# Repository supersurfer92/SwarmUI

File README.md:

# BadukBot: Swarming robots to play the game Go/Baduk

Based on Zooids: Building Blocks for Swarm User Interfaces

Zooids, an open-source open-hardware platform for developing tabletop swarm interfaces, consist of a collection of custom-designed wheeled micro robots (each 2.6 cm in diameter), a radio base-station, a highspeed DLP structured light projector for optical tracking, and a software framework for application development and control.

Initial sketch of the redesigned Zooid, the BadukBot:

Revision 3 of the new pcb:

Original board:

BadukBot is based on Zooid software and hardware modified to play the game Go/Baduk/Weiqi. https://en.wikipedia.org/wiki/Go_(game)

Zooids in action: https://www.youtube.com/watch?time_continue=125&v=ZVdAfDMP3m0

## Hardware

The original Zooids are small custom-made robots as shown above; their dimensions are 26 mm in diameter, 21 mm in height
and they weight about 12 g. Each robot is powered by a 100 mAh LiPo battery and uses motor driven wheels. They contain a flexible elctrode for capacitive touch sensing. It communicates with the main computer through a NRF24L01+ chip on a separate receiver. Currently the limit for bots per receiver is 10. More can be added at a cost to performance/communication speed.

BadukBots are 22.5 mm in diameter and ~50 mm in height. Each bot is powered by a 200 mAh lipo battery with motor driven wheels.

The original Zooid files have been converted from Altium schematics to KiCAD from scratch based on the original Zooid schematic pdf (original files break when converted.) The new PCBs and schematics are located in the BadukBot directory. The Proto...BOM consolidates the components for bots, Receivers, chargers, and tools required into one sheet. The new BOM is mostly the same with changes to include prices, links, and modifications to quantities to make 81 (for a 9x9 board) and 361 (for a 19x19 board) bots in the Master BOM spreadsheet.

The PCB is designed using KiCAD and FreeRouting. The 3D files are created in MODO. The BadukBot breaks the design into 3 single boards that encase the battery to both make it possible to reflow at home and reduce the foot print to 22.5 mm from the Zooid's 26 mm (go stones are 22.5 mm and allow for a full 19x19 board to fit in the projection area.) Dimensions for bots and the playspace are based on https://senseis.xmp.net/?EquipmentDimensions and will be scaled if needed accordingly.

We may try other DLP Lightcrafter EVMs to reduce cost ($140 vs $1400.)

### Tracking
The system uses a projector-based tracking system for robot position tracking as shown below. Using a high frame rate (3000Hz) projector (DLP LightCrafter Evaluation Module) from Texas Instruments Inc., a sequence of gray-coded patterns are projected onto a flat surface. Then, the photodiodes on the robot independently decodes into a location within the projected area. 
The instruction for setting up this projector-based tracking system is included in the repository. 
There are other DLPLCEVM projectors available at lower resolutions and refresh rates ranging from $140 to $1600.

The play area will be mapped to make a main play area, a go bowl area and a capture pieces area

## Software

The communication structure consists of four main layers from highest to lowest level: Application, Simulation, Server, and Hardware. 

At the application level, the desired positions of the robots are computed. These desired positions are transmitted to
the simulation layer through a network socket. The application programmer can choose between two control strategies:
Proportional-Integral-Derivative (PID) position control or Hybrid Reciprocal Velocity Obstacles (HRVO) combined
with PID (these options are explained in the next paragraphs). Based on the chosen control strategy, the simulation layer
computes the goal positions of the robots, either final positions for PID or intermediate points for HRVO, and sends them to
the server. Finally, the server layer dispatches commands to the individual zooids, while at the same time monitoring their status and position.

Each robot independently controls its motion through a PID controller based on the state machine shown below. Given a final goal, the robot initially turns itself in the right direction and, once aligned, accelerates to its user-defined preferred speed. When it reaches the speed, it maintains it with a PID control on the orientation to ensure its direction towards the final goal. When a new incremental goal is given, it will still move at same speed but the PID control on orientation will direct the robot towards the new intermediate goal. When the robot arrives within 5 cm of the final goal, it slows down to its minimum velocity and once within 1 cm of the final goal, it stops and orients itself as commanded by the application programmer. To enable smooth transitions between the incremental goal positions, robots are given their next position at 60 Hz.

The modified software for playing Go using SwarmUI (GoSwarm) can be found at https://github.com/nheyn/GoSwarm and https://github.com/nheyn/react-swarm-ui and modified firmware will be maintained in this repo.

Goals include:

-defined areas for the bots including game play area on a grid

-automatically arranging bots to a Go bowl area

-automatically moving captured stones/bots to a defined captured bowl area

-queueing bots for the next turn

-game play rules like passing/resigning

-automatic scoring (and the ability to adjust captured areas)

-the ability to show which player is the winner (2 bots emerge from the winners go bowl, 1 from the loser after both sides pass or one resigns)

Resources and goals for features can be found at https://github.com/supersurfer92/SwarmUI-BadukBots/blob/master/Software/Go%20Features%2C%20Programming%20Gits%2C%20and%20theory.txt

GoSwarm has rewritten the ZooidManager program from C++ to Java and is currently developing swarming functions

## Acknowledgments 

BadukBot and GoSwarm/react-SwarmUI is a hobby project created by Caleb Cover and Nick Heyn based on SwarmUI.

The original SwarmUI project (https://github.com/ShapeLab/SwarmUI) is a joint work between the Shape Lab at Stanford University (USA) and the Aviz team at Inria (France). It was partially funded by the Région Ile de France, DIM ISC-PIF. We would also like to thank Alexa Siu, Shenli Yuan, Ernesto Ramirez and Pham Minh Hieu for investing so much time and efforts in making this work possible. 

The original licenses are retained where applicable and the licenses used for new hardware developed will use a license that follows the Open Source Hardware Association definition of Open Source Hardware (https://www.oshwa.org/definition/.)

<br />This work is licensed under a <a rel="license" href="http://creativecommons.org/licenses/by-sa/4.0/">Creative Commons Attribution-ShareAlike 4.0 International License</a>.

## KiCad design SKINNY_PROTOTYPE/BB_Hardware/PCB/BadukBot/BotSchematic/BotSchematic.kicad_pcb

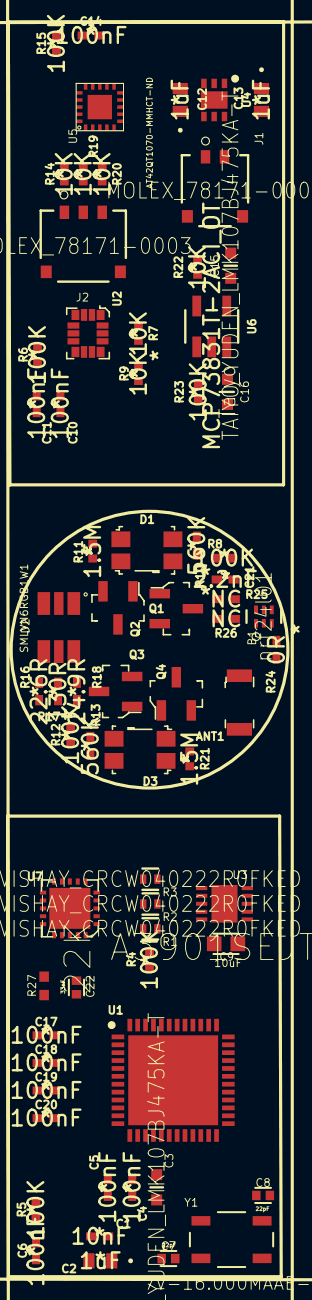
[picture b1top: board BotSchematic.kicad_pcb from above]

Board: 4 copper layers, 68 parts (0 on the bottom side), 52 nets, no tracks yet.

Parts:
ANT1: Antenna; Antenna_1.6x3.2mm_2450AT18A100E
B1: nrf24l01; JOHANSON_2450BM14A0002T_0
C1: 10nF; C0402C103J3RACTU
C2, C12, C13: 1uF; 0603ZD105KAT2A
C3, C15: TAIYO_YUDEN_LMK107BJ475KA-T; TAIYO_YUDEN_LMK107BJ475KA-T_0
C4, C5, C6, C10, C11, C14, C17, C18, C19, C20: 100nF; C0402C104K4RACTU
C7, C8: 22pF; CAPC1005X55N
C9: 10uF; CAPC1608X9N
C16: Taiyo; TAIYO_YUDEN_LMK107BJ475KA-T_0
C21: 2.2nF; C0402C222K5RACTU
C22: 33nF; CAPC1005X55N
D1, D3: PD15-22C_TR8; SMD-4_3.3x2.8_PD15-22C_TR8
D2: SMLVN6RGB1W1; LED310X280X60-6N
J1: MOLEX_78171-0002; MOLEX_78171-0002_0
J2: MOLEX_78171-0003; MOLEX_78171-0003_0
Q1, Q2, Q3, Q4: MMBT3904LT1G; SOT-23-3
R1, R2, R3: VISHAY_CRCW040222R0FKED; VISHAY_CRCW040222R0FKED_0
R4, R5, R6, R8, R12, R15, R23: 100K; CRCW0402100KFKED
R7, R9, R14, R19, R20, R22: 10K; CRCW040210K0FKED
R10, R13: 560K; RC0402FR-07560KL
R11, R21: 1.5M; CRCW04021M50FKED
R16: 22.6R; ERJ-2RKF22R6X
R17: 130R; ERJ-2RKF1300X
R18: 24.9R; ERJ-2RKF24R9X
R24: 0R; ERJ-2GE0R00X
R25, R26: NC; ERJ-2GE0R00X
R27: 22K; RESC1005X40N
U1: STM32F051C8U6; QFN50P700X700X65-49N-D
U2: LSM6DS3; LGA-14L_2.5x3mm__LSM6DS3
U3: A3901SEJTR-T; DFN300X300X75-11N
U4: ADP122ACPZ-3.3-R7; SON65P200X200X60-7N-D
U5: AT42QT1070-MMHCT-ND; VQFN_20PAD
U6: MCP73831T-2ACI_OT; MCP73831T-2ACI&slash_OT
U7: NRF24L01P-R7; QFN-20-1EP_4x4mm_RevA
Y1: 7V-16.000MAAE-T; OSCCC500X320X105N

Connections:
+3V3: C1.1, C2.1, C3.1, C4.1, C5.1, C9.1, C10.1, C11.1, C13.1, C14.1, C17.2, C18.2, C19.2, C20.2, D1.K, D2.1, D2.2, D2.3, D3.K, R5.2, R6.2, R7.2, R8.2, R9.2, R10.2, R12.2, R13.2, R15.2, R23.1, U1.9, U1.24, U1.48, U2.5, U2.8, U2.12, U3.8, U4.1, U5.9, U5.13, U7.7, U7.15, U7.18
+BATT: C12.1, C16.1, J1.1, U1.1, U4.4, U4.6, U6.3
ANT1: B1.4, U7.12
ANT2: B1.3, U7.13
CSN: U1.14, U7.2
Charging: R23.2, U6.1
GND: B1.2, C1.2, C2.2, C3.2, C4.2, C5.2, C6.2, C7.2, C8.2, C9.2, C10.2, C11.2, C12.2, C13.2, C14.2, C15.2, C16.2, C17.1, C18.1, C19.1, C20.1, C21.2, C22.2, J1.2, Q1.2, Q2.2, Q3.2, Q4.2, R4.2, R11.2, R21.1, R22.1, R25.2, R26.2, R27.1, U1.8, U1.23, U1.47, U1.49, U2.1, U2.2, U2.3, U2.6, U2.7, U3.3, U4.3, U5.8, U5.11, U6.2, U7.8, U7.14, U7.17, U7.20, U7.21
IMU_INT: R6.1, U1.25, U2.4
MCU_X1_16MHZ: C7.1, U1.5, Y1.1
MCU_X2_16MHZ: C8.1, U1.6, Y1.3
MISO: U1.16, U7.5
MOSI: U1.17, U7.4
MOTOR_CONTROL1: U1.10, U3.1
MOTOR_CONTROL2: U1.11, U3.2
MOTOR_CONTROL3: U1.12, U3.4
MOTOR_CONTROL4: U1.13, U3.5
NRST: C6.1, R2.2, R5.1
unnamed: ANT1.1, R24.1, R26.1
unnamed: B1.1, R24.2, R25.1
unnamed: C15.1, U6.4
unnamed: C22.1, U7.19
unnamed: D1.A, Q2.1, R11.1
unnamed: D2.4, R16.2
unnamed: D2.5, R17.2
unnamed: D2.6, R18.2
unnamed: D3.A, Q4.1, R21.2
unnamed: J2.1, R14.2
unnamed: J2.2, R19.2
unnamed: J2.3, R20.2
unnamed: Q1.1, Q2.3, R10.1
unnamed: Q3.1, Q4.3, R13.1
unnamed: R4.1, U1.44
unnamed: R14.1, U5.4
unnamed: R19.1, U5.3
unnamed: R20.1, U5.2
unnamed: R22.2, U6.5
unnamed: R27.2, U7.16
PHOTODIODE_1: Q1.3, R8.1, U1.46
PHOTODIODE_2: Q3.3, R12.1, U1.19
RADIO_CE: U1.18, U7.1
RADIO_CLK: U1.29, U7.10
RADIO_IRQ: U1.38, U7.6
RGBLED1: R17.1, U1.31
RGBLED2: R16.1, U1.32
RGBLED3: R18.1, U1.30
SCK: U1.15, U7.3
SCL: R9.1, U1.21, U1.42, U2.13, U5.15
SDA: R7.1, U1.22, U1.43, U2.14, U5.12
SWCLK: R3.2, U1.37
SWDIO: R1.2, U1.34
VDD_PA: B1.5, C21.1, U7.11
~TOUCH_CHG~: R15.1, U5.14

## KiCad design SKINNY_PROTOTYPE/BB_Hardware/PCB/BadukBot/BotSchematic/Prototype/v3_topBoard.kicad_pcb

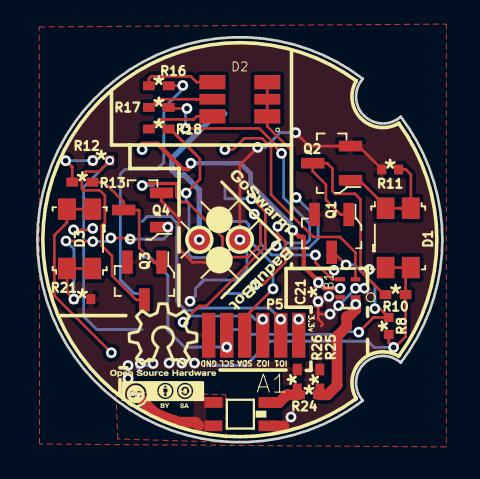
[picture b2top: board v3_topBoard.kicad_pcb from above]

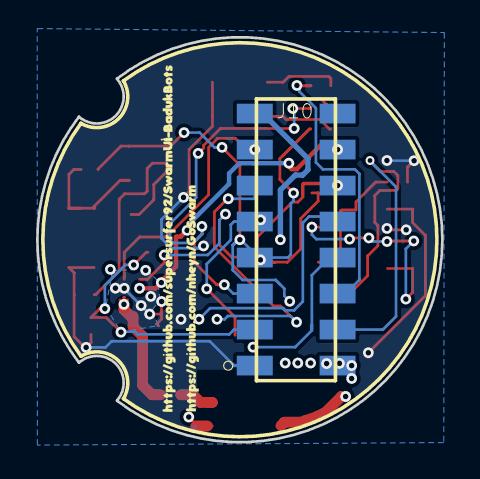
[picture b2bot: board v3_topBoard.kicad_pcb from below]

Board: 2 copper layers, 22.5 x 22.5 mm, 28 parts (2 on the bottom side), 24 nets.

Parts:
A1: 2450AT18D0100E; DFN320X160X120-4RN
B1: nrf24l01; JOHANSON_2450BM14A0002T_0
C21: 2.2nF; C0402C222K5RACTU
D1, D3: PD15-22C_TR8; SMD-4_3.3x2.8_PD15-22C_TR8
D2: SMLVN6RGB1W1; LED310X280X60-6N
G1: LOGO; BadukBot-GoSwarm
G2: LOGO; OpenHardwareLogo
G7: LOGO; links_20mm
J10: A316DA2SV71; A13_1
P4: Conn01x02Female; Conn_01x02_Female
P5: Pads; ExternalPort
Q1, Q2, Q3, Q4: MMBT3904LT1G; SOT-23-3
R8, R12: 100K; CRCW0402100KFKED
R10, R13: 560K; RC0402FR-07560KL
R11, R21: 1.5M; CRCW04021M50FKED
R16: 22.6R; ERJ-2RKF22R6X
R17: 130R; ERJ-2RKF1300X
R18: 24.9R; ERJ-2RKF24R9X
R24: 0R; ERJ-2GE0R00X
R25, R26: NC; ERJ-2GE0R00X

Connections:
1a33v: D1.K, D2.1, D2.2, D2.3, D3.K, J10.1, P5.1, R8.2, R10.2, R12.2, R13.2
2aGND: A1.2, A1.3, A1.4, B1.2, C21.2, J10.2, J10.16, P4.2, P5.6, Q1.2, Q2.2, Q3.2, Q4.2, R11.2, R21.1, R25.2, R26.2
3aPHOTODIODE1: J10.3, Q1.3, R8.1
4aPHOTODIODE2: J10.4, Q3.3, R12.1
5aRGBLED1: J10.5, R17.1
6aRGBLED2: J10.6, R16.1
7aRGBLED3: J10.7, R18.1
12aA1: B1.4, J10.12
13aA2: B1.3, J10.13
14aVDDPA: B1.5, C21.1, J10.14
15aP41: J10.15, P4.1
unnamed: A1.1, R24.1, R26.1
unnamed: B1.1, R24.2, R25.1
unnamed: D1.A, Q2.1, R11.1
unnamed: D2.4, R16.2
unnamed: D2.5, R17.2
unnamed: D2.6, R18.2
unnamed: D3.A, Q4.1, R21.2
unnamed: J10.8, P5.5
unnamed: J10.9, P5.4
unnamed: J10.10, P5.2
unnamed: J10.11, P5.3
unnamed: Q1.1, Q2.3, R10.1
unnamed: Q3.1, Q4.3, R13.1

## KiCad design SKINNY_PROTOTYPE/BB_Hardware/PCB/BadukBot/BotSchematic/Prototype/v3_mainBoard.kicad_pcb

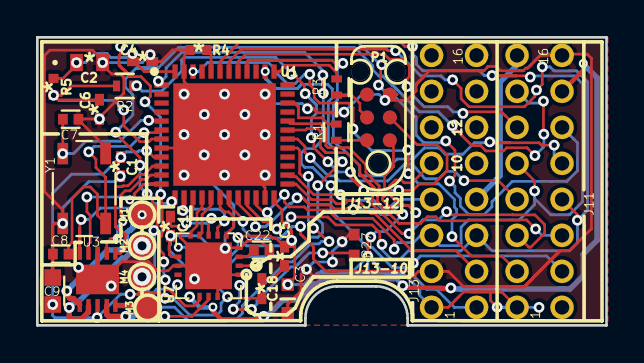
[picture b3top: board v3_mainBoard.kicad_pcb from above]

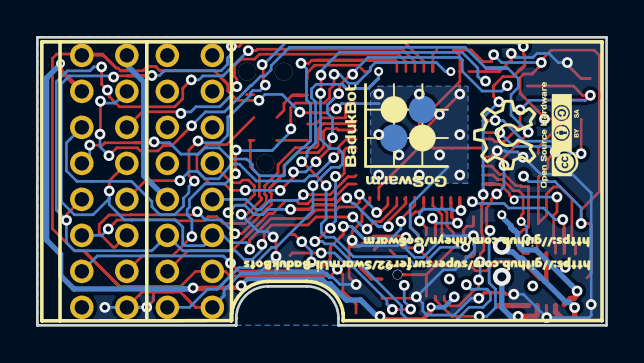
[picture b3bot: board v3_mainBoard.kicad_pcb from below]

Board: 2 copper layers, 31.6 x 16.0 mm, 33 parts (4 on the bottom side), 44 nets.

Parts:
C1: 10nF; C0402C103J3RACTU
C2: 1uF; 0603ZD105KAT2A
C3: TAIYO_YUDEN_LMK107BJ475KA-T; TAIYO_YUDEN_LMK107BJ475KA-T_0
C4, C5, C6, C17, C18: 100nF; C0402C104K4RACTU
C7, C8: 22pF; CAPC1005X55N
C9: 10uF; CAPC1608X9N
C22: 33nF; CAPC1005X55N
G1: LOGO; BadukBot-GoSwarm
G2: LOGO; OpenHardwareLogo
G5: LOGO; links_20mm
J11, J13: 62401621722; 0877601616
M1: Pos1a; TESTPOINT-50MIL
M2: Neg1a; TESTPOINT-50MIL
M3: Pos2a; TESTPOINT-50MIL
M4: Neg2a; TESTPOINT-50MIL
P1: SWDPads; SWD_6pin
P4: Conn_01x02_Female
R1, R2, R3: VISHAY_CRCW040222R0FKED; VISHAY_CRCW040222R0FKED_0
R4, R5: 100K; CRCW0402100KFKED
R27: 22K; RESC1005X40N
U1: STM32F051C8U6; QFN50P700X700X65-49N-D
U3: A3901SEJTRT; DFN300X300X75-11N
U7: NRF24L01PR7; QFN-20-1EP_4x4mm_RevA
Y1: 7V16000MAAET; OSCCC500X320X105N

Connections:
1b33v: C1.1, C2.1, C3.1, C4.1, C5.1, C9.1, C17.2, C18.2, J11.1, J13.1, P1.1, R5.2, U1.9, U1.24, U1.48, U3.8, U7.7, U7.15, U7.18
2bGND: C1.2, C2.2, C3.2, C4.2, C5.2, C6.2, C7.2, C8.2, C9.2, C17.1, C18.1, C22.2, J11.16, J13.3, P1.5, R4.2, R27.1, U1.8, U1.23, U1.47, U1.49, U3.3, U3.11, U7.8, U7.14, U7.17, U7.20, U7.21, Y1.2, Y1.4
3bPHOTODIODE1: J11.3, U1.46
4bPHOTODIODE2: J11.4, U1.19
5bRGBLED1: J11.5, U1.31
6bRGBLED2: J11.6, U1.32
7bRGBLED3: J11.7, U1.30
8bIO1: J11.10, U1.40
9bIO2: J11.11, U1.41
10bSDA: J11.9, J13.5, U1.22, U1.43
11bSCL: J11.8, J13.6, U1.21, U1.42
12bA1: J11.12, U7.12
13bA2: J11.13, U7.13
14bVDDPA: J11.14, U7.11
15bP41: J11.15, J13.8
22bVBAT: J13.2, U1.1
24bIMUINT: J13.4, U1.25
27bCHARGING: J13.7, U1.26
CSN: U1.14, U7.2
MCUX116MHZ: C7.1, U1.5, Y1.1
MCUX216MHZ: C8.1, U1.6, Y1.3
MISO: U1.16, U7.5
MOSI: U1.17, U7.4
MOTORCONTROL1: U1.10, U3.1
MOTORCONTROL2: U1.11, U3.2
MOTORCONTROL3: U1.12, U3.4
MOTORCONTROL4: U1.13, U3.5
NRST: C6.1, R2.2, R5.1, U1.7
unnamed: C22.1, U7.19
unnamed: M1.1, U3.6
unnamed: M2.1, U3.7
unnamed: M3.1, U3.10
unnamed: M4.1, U3.9
unnamed: P1.2, R1.1
unnamed: P1.3, R2.1
unnamed: P1.4, R3.1
unnamed: R4.1, U1.44
unnamed: R27.2, U7.16
RADIOIRQ: U1.38, U7.6
RADIO_CE: U1.18, U7.1
SCK: U1.15, U7.3
SWCLK: R3.2, U1.37
SWDIO: R1.2, U1.34
~29bTOUCHCHG~: J13.9, U1.20

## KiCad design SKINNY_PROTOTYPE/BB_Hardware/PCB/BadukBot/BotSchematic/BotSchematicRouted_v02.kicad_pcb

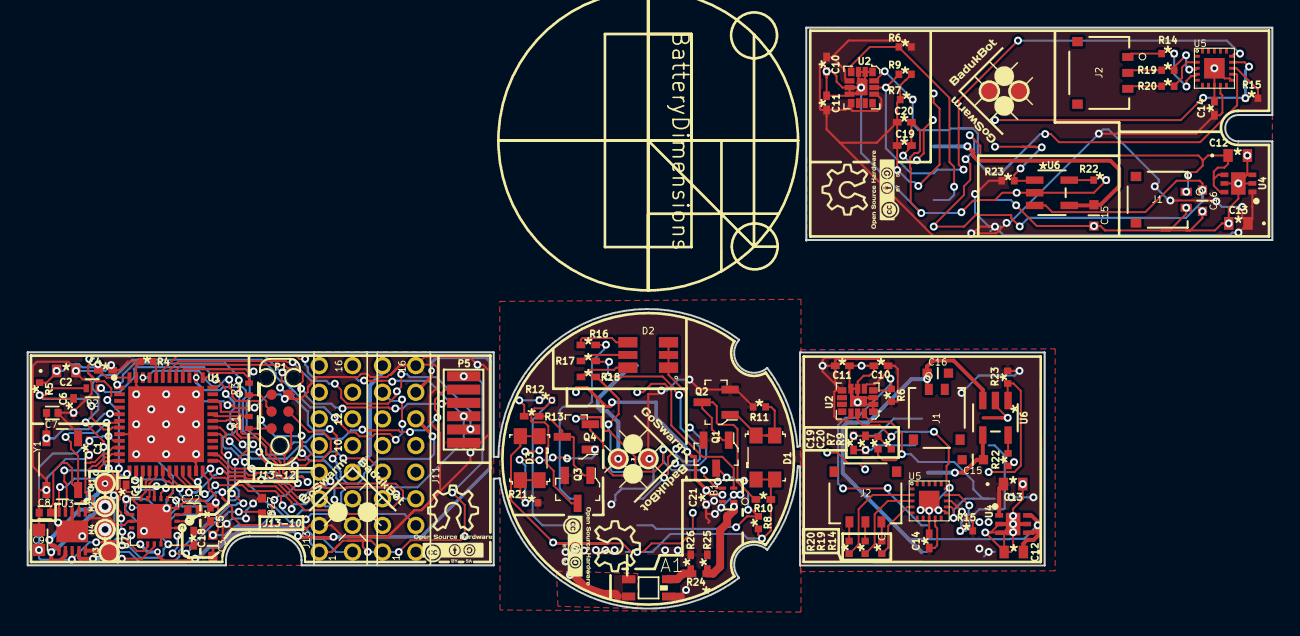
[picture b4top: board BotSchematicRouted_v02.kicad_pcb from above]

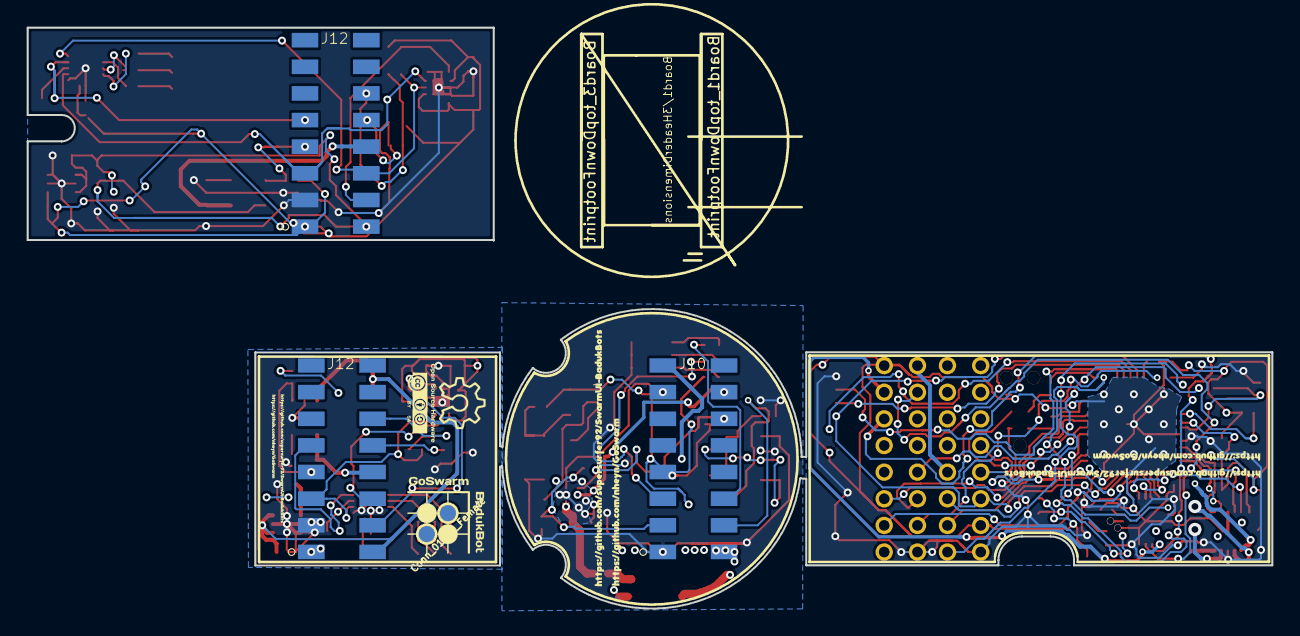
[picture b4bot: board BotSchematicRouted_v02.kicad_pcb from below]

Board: 2 copper layers, 93.5 x 43.6 mm, 117 parts (8 on the bottom side), 106 nets.

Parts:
A1: 2450AT18D0100E; DFN320X160X120-4RN
B1: nrf24l01; JOHANSON_2450BM14A0002T_0
C1: 10nF; C0402C103J3RACTU
C2, C12, C12#2, C13, C13#2: 1uF; 0603ZD105KAT2A
C3, C15, C15#2: TAIYO_YUDEN_LMK107BJ475KA-T; TAIYO_YUDEN_LMK107BJ475KA-T_0
C4, C5, C6, C10, C10#2, C11, C11#2, C14, C14#2, C17, C18: 100nF; C0402C104K4RACTU
C7, C8: 22pF; CAPC1005X55N
C9: 10uF; CAPC1608X9N
C16, C16#2: Taiyo; TAIYO_YUDEN_LMK107BJ475KA-T_0
C19, C19#2: 10nF; C0402C104K4RACTU
C20, C20#2: 1nF; C0402C104K4RACTU
C21: 2.2nF; C0402C222K5RACTU
C22: 33nF; CAPC1005X55N
D1, D3: PD15-22C_TR8; SMD-4_3.3x2.8_PD15-22C_TR8
D2: SMLVN6RGB1W1; LED310X280X60-6N
G1, G1#2, G1#3, G11: LOGO; BadukBot-GoSwarm
G2, G2#2, G2#3, G10: LOGO; OpenHardwareLogo
G5, G7: LOGO; links_20mm
J1, J1#2: MOLEX781710002; MOLEX_78171-0002_0
J2, J2#2: MOLEX781710003; MOLEX_78171-0003_0
J10, J12, J12#2: A316DA2SV71; A13_1
J11: 62401621722; 0877601616
J13: 0877601616
M1: Pos1a; TESTPOINT-50MIL
M2: Neg1a; TESTPOINT-50MIL
M3: Pos2a; TESTPOINT-50MIL
M4: Neg2a; TESTPOINT-50MIL
P1: SWDPads; SWD_6pin
P4: Conn01x02Female; Conn_01x02_Female
P5: Pads; ExternalPort
P10: Conn_01x02_Female
Q1, Q2, Q3, Q4: MMBT3904LT1G; SOT-23-3
R1, R2, R3: VISHAY_CRCW040222R0FKED; VISHAY_CRCW040222R0FKED_0
R4, R5, R6, R6#2, R8, R12, R15, R15#2, R23, R23#2: 100K; CRCW0402100KFKED
R7, R7#2, R9, R9#2, R14, R14#2, R19, R19#2, R20, R20#2, R22, R22#2: 10K; CRCW040210K0FKED
R10, R13: 560K; RC0402FR-07560KL
R11, R21: 1.5M; CRCW04021M50FKED
R16: 22.6R; ERJ-2RKF22R6X
R17: 130R; ERJ-2RKF1300X
R18: 24.9R; ERJ-2RKF24R9X
R24: 0R; ERJ-2GE0R00X
R25, R26: NC; ERJ-2GE0R00X
R27: 22K; RESC1005X40N
TESTPOINT-50MIL, TESTPOINT-50MIL#2: VAL**; TESTPOINT-50MIL
U1: STM32F051C8U6; QFN50P700X700X65-49N-D
U2, U2#2: LSM6DS3; LGA-14L_2.5x3mm__LSM6DS3
U3: A3901SEJTRT; DFN300X300X75-11N
U4, U4#2: ADP122ACPZ33R7; SON65P200X200X60-7N-D
U5, U5#2: AT42QT1070MMHCTND; VQFN_20PAD
U6, U6#2: MCP73831T2ACIOT; MCP73831T-2ACI&slash_OT
U7: NRF24L01PR7; QFN-20-1EP_4x4mm_RevA
Y1: 7V16000MAAET; OSCCC500X320X105N

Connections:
1a33v: D1.K, D2.1, D2.2, D2.3, D3.K, J10.1, R8.2, R10.2, R12.2, R13.2
1b33v: C1.1, C2.1, C3.1, C4.1, C5.1, C9.1, C17.2, C18.2, J11.1, J13.1, P1.1, P5.1, R5.2, U1.9, U1.24, U1.48, U3.8, U7.7, U7.15, U7.18
2aGND: A1.2, A1.3, A1.4, B1.2, C21.2, J10.2, P4.2, Q1.2, Q2.2, Q3.2, Q4.2, R11.2, R21.1, R25.2, R26.2
2bGND: C1.2, C2.2, C3.2, C4.2, C5.2, C6.2, C7.2, C8.2, C9.2, C17.1, C18.1, C22.2, J11.16, J13.3, P1.5, P5.6, R4.2, R27.1, U1.8, U1.23, U1.47, U1.49, U3.3, U3.11, U7.8, U7.14, U7.17, U7.20, U7.21, Y1.2, Y1.4
3aPHOTODIODE1: J10.3, Q1.3, R8.1
3bPHOTODIODE1: J11.3, U1.46
4aPHOTODIODE2: J10.4, Q3.3, R12.1
4bPHOTODIODE2: J11.4, U1.19
5aRGBLED1: J10.5, R17.1
5bRGBLED1: J11.5, U1.31
6aRGBLED2: J10.6, R16.1
6bRGBLED2: J11.6, U1.32
7aRGBLED3: J10.7, R18.1
7bRGBLED3: J11.7, U1.30
8bIO1: P5.2, U1.40
9bIO2: P5.3, U1.41
10bSDA: J13.5, P5.4, U1.22, U1.43
11bSCL: J13.6, P5.5, U1.21, U1.42
12aA1: B1.4, J10.12
12bA1: J11.12, U7.12
13aA2: B1.3, J10.13
13bA2: J11.13, U7.13
14aVDDPA: B1.5, C21.1, J10.14
14bVDDPA: J11.14, U7.11
15aP41: J10.15, P4.1
15bP41: J11.15, J13.8
21a3.3v: R7.2, R7#2.2, R9.2, R9#2.2
21a33v: C10.1, C10#2.1, C11.1, C11#2.1, C13.1, C13#2.1, C14.1, C14#2.1, C19.2, C19#2.2, C20.2, C20#2.2, J12.1, J12#2.1, R6.2, R6#2.2, R15.2, R15#2.2, R23.1, R23#2.1, U2.5, U2.8, U2.12, U2#2.5, U2#2.8, U2#2.12, U4.1, U4#2.1
22aVBAT: C12.1, C12#2.1, C16.1, C16#2.1, J1.1, J1#2.1, J12.2, J12#2.2, U4.4, U4.6, U4#2.4, U4#2.6, U6.3, U6#2.3
22bVBAT: J13.2, U1.1
23aGround: C10.2, C10#2.2, C11.2, C11#2.2, C12.2, C12#2.2, C13.2, C13#2.2, C14.2, C14#2.2, C15.2, C15#2.2, C16.2, C16#2.2, C19.1, C19#2.1, J1.2, J1#2.2, J12.3, J12#2.3, R22.1, R22#2.1, U2.1, U2.2, U2.3, U2.6, U2.7, U2#2.1, U2#2.2, U2#2.3, U2#2.6, U2#2.7, U4.2, U4.3, U4.5, U4.7, U4#2.2, U4#2.3, U4#2.5, U4#2.7, U5.8, U5.9, U5.11, U5.13, U5.44, U5#2.8, U5#2.9, U5#2.11, U5#2.13, U5#2.44, U6.2, U6#2.2
23a_Ground: C20.1, C20#2.1
24aIMUINT: J12.4, J12#2.4, R6.1, R6#2.1, U2.4, U2#2.4
24bIMUINT: J13.4, U1.25
25aSDA: J12.5, J12#2.5, R7.1, R7#2.1, U2.14, U2#2.14, U5.12, U5#2.12
26aSCL: J12.6, J12#2.6, R9.1, R9#2.1, U2.13, U2#2.13, U5.15, U5#2.15
27aCHARGING: J12.7, J12#2.7, R23.2, R23#2.2, U6.1, U6#2.1
27bCHARGING: J13.7, U1.26
28aP41: C15.1, C15#2.1, J12.8, J12#2.8, U6.4, U6#2.4
CSN: U1.14, U7.2
MCUX116MHZ: C7.1, U1.5, Y1.1
MCUX216MHZ: C8.1, U1.6, Y1.3
MISO: U1.16, U7.5
MOSI: U1.17, U7.4
MOTORCONTROL1: U1.10, U3.1
MOTORCONTROL2: U1.11, U3.2
MOTORCONTROL3: U1.12, U3.4
MOTORCONTROL4: U1.13, U3.5
NRST: C6.1, R2.2, R5.1, U1.7
unnamed: A1.1, R24.1, R26.1
unnamed: B1.1, R24.2, R25.1
unnamed: C22.1, U7.19
unnamed: D1.A, Q2.1, R11.1
unnamed: D2.4, R16.2
unnamed: D2.5, R17.2
unnamed: D2.6, R18.2
unnamed: D3.A, Q4.1, R21.2
unnamed: J1.3, J1#2.3
unnamed: J1.4, J1#2.4
unnamed: J2.1, J2#2.1, R14.2, R14#2.2
unnamed: J2.2, J2#2.2, R19.2, R19#2.2
unnamed: J2.3, J2#2.3, R20.2, R20#2.2
unnamed: J2.4, J2#2.4
unnamed: J2.5, J2#2.5
unnamed: J12.10, J12#2.10
unnamed: J12.11, J12#2.11
unnamed: J12.12, J12#2.12
unnamed: J12.13, J12#2.13
unnamed: J12.14, J12#2.14
unnamed: J12.15, J12#2.15
unnamed: J12.16, J12#2.16
unnamed: M1.1, U3.6
unnamed: M2.1, U3.7
unnamed: M3.1, U3.10
unnamed: M4.1, U3.9
unnamed: P1.2, R1.1
unnamed: P1.3, R2.1
unnamed: P1.4, R3.1
unnamed: Q1.1, Q2.3, R10.1
unnamed: Q3.1, Q4.3, R13.1
unnamed: R4.1, U1.44
unnamed: R14.1, R14#2.1, U5.4, U5#2.4
unnamed: R19.1, R19#2.1, U5.3, U5#2.3
unnamed: R20.1, R20#2.1, U5.2, U5#2.2
unnamed: R22.2, R22#2.2, U6.5, U6#2.5
unnamed: R27.2, U7.16
unnamed: U2.9, U2#2.9
unnamed: U2.10, U2#2.10
unnamed: U2.11, U2#2.11
unnamed: U5.1, U5#2.1
unnamed: U5.5, U5#2.5
unnamed: U5.6, U5#2.6
unnamed: U5.7, U5#2.7
unnamed: U5.10, U5#2.10
unnamed: U5.16, U5#2.16
unnamed: U5.17, U5#2.17
unnamed: U5.18, U5#2.18
unnamed: U5.19, U5#2.19
unnamed: U5.20, U5#2.20
RADIOIRQ: U1.38, U7.6
RADIO_CE: U1.18, U7.1
SCK: U1.15, U7.3
SWCLK: R3.2, U1.37
SWDIO: R1.2, U1.34
~29aTOUCHCHG~: J12.9, J12#2.9, R15.1, R15#2.1, U5.14, U5#2.14
~29bTOUCHCHG~: J13.9, U1.20

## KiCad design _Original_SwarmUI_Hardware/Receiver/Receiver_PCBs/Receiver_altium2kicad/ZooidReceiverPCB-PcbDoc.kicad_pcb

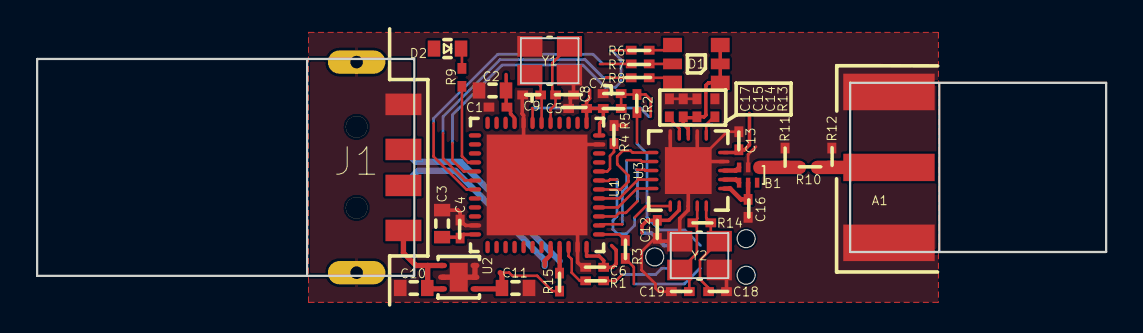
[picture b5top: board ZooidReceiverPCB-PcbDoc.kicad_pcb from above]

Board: 4 copper layers, 59.4 x 13.3 mm, 45 parts (1 on the bottom side), 37 nets.

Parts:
A1: JOHNSON 142-4701-801 SMA FEMELLE REVERSE POLARITY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; 142-4701-801
B1: Johanson Technology Impedance Matched Balun Filte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; 2450BM14A0002
C1, C4, C5, C6, C7, C8, C9, C12, C13, C14, C15, C16, C17, C18, C19: 0402
C2, C3, C10, C11: 0603
D1: ROHM SMLVN6RGB1W1 LED Tri-Color Blue/Green/Red Ch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; 3.5x2.8 mm 6-SMD
D2: BRIGHT BLUE LED 20mA; 0603 - LED
J1: Molex USB 2.0 Connector Plug USB Type A; 48037-2200
P1: TagConnect TC2030-IDC-NL SWD Programming Connector; TC2030-IDC-NL
R1, R2, R3, R4, R5, R6, R7, R8, R9, R10, R13, R14, R15: 0402
R11, R12: NOT CONNECTED; 0402 - NOBODY
U1: STMICROELECTRONICS STM32F103CBU6 ARM Cortex-M3, 7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; QFN50P700X700X60_HS-49L
U2: Analog Devices ADP122ACPZ-3.3-R7 - 5.5 V Input, 3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; LFCSP-6 2.0X2.0X0.55
U3: Nordic Semi Ultra low power 2.4GHz RF Transceiver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; QFN50P400X400X95_HS-21L
Y1, Y2: TXC - 7V-16.000MAAE-T, 16MHZ, 30PPM, 12PF - CRYST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; 3.2x2.5 CRYSTAL

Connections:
+3.3V: C1.2, C2.2, C3.2, C4.2, C5.2, C6.2, C11.2, C12.2, C13.2, C14.2, C15.2, D1.1, D1.2, D1.3, D2.1, P1.1, R5.2, R15.2, U1.1, U1.9, U1.24, U1.36, U1.48, U2.1, U3.7, U3.15, U3.18
ANT1: B1.4, U3.12
ANT2: B1.3, U3.13
GND: A1.2, B1.2, C1.1, C2.1, C3.1, C4.1, C5.1, C6.1, C7.1, C8.1, C9.1, C10.1, C11.1, C12.1, C13.1, C14.1, C15.1, C16.1, C17.1, C18.1, C19.1, J1.4, J1.5, P1.5, R4.1, R11.1, R12.1, R13.1, U1.8, U1.23, U1.35, U1.47, U1.49, U2.2, U2.3, U2.5, U2.7, U3.8, U3.14, U3.17, U3.20, U3.21, Y1.2, Y1.4, Y2.2, Y2.4
MCU_X1_16MHZ: C8.2, U1.5, Y1.1
MCU_X2_16MHZ: C9.2, U1.6, Y1.3
NRST: C7.2, R2.1, R5.1, U1.7
NetA1_1: A1.1, R10.2, R12.2
NetB1_1: B1.1, R10.1, R11.2
NetC17_2: C17.2, U3.19
NetD1_4: D1.4, R6.2
NetD1_5: D1.5, R7.2
NetD1_6: D1.6, R8.2
NetD2_2: D2.2, R9.2
NetP1_2: P1.2, R1.2
NetP1_3: P1.3, R2.2
NetP1_4: P1.4, R3.2
NetR4_2: R4.2, U1.44
NetR13_2: R13.2, U3.16
RADIO_SPI.CE: U1.42, U3.1
RADIO_SPI.CSN: U1.38, U3.2
RADIO_SPI.IRQ: U1.43, U3.6
RADIO_SPI.MISO: U1.40, U3.5
RADIO_SPI.MOSI: U1.41, U3.4
RADIO_SPI.SCK: U1.39, U3.3
RADIO_X1_16MHZ: C18.2, R14.1, U3.10, Y2.3
RADIO_X2_16MHZ: C19.2, R14.2, U3.9, Y2.1
RGBLED1: R7.1, U1.19
RGBLED2: R6.1, U1.17
RGBLED3: R8.1, U1.18
STATUS_LED: R9.1, U1.16
SWCLK: R3.1, U1.37
SWDIO: R1.1, U1.34
USB_D_N: J1.2, U1.32
USB_D_P: J1.3, R15.1, U1.33
VDD_PA: B1.5, C16.2, U3.11
VUSB: C10.2, J1.1, U2.4, U2.6

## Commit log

2018-10-20 Add files via upload
    Master BOM files for Zooids, Receiver, and Charger including supplier links, prices, tools needed, PCB stencils, etc.
    Sheet is for making 81 and 361 Zooids
2018-10-20 Charger PCB Gerbers .zip
    Zipped Charging pad gerbers file to make it easy to upload to OSH Park, PCB Way, Seeed, etc.
    Issue with file on OSH Park for drill holes. Not sure if other PCB providers get the same errors when being uploaded.
2018-10-20 Zooid and Receiver zipped Gerber files
    Zipped Zooid and Receiver gerber files to make it easy to upload to OSH Park, PCB Way, Seeed, etc.
    Issue with file on OSH Park for drill holes. Not sure if other PCB providers get the same errors when being uploaded.
    When using the Zooid files to generate stencils not sure if bottom stencil needs to be mirrored for use with OSH Stencils solder paste stencil. Same for receiver.
2018-10-20 Missing coordinates for slots to be drilled out
    Slots don't show when loading into previews like Gerbv
2018-10-20 Create ZooidGerbers
2018-10-20 blank file delete
2018-10-20 Drill gerber fixed, need to fix slot drill gerber
2018-10-20 Drill gerber fixed
2018-10-20 Folder structure organization
2018-10-20 Deprecated, use xls file
2018-10-20 Tools, charger, receiver, etc updated
2018-10-20 Drill Gerber scale corrected
2018-10-20 Drill gerber updated
2018-10-20 Updates to parts, tools, quantities, sources
2018-10-20 Charging pad gerbers
2018-10-20 Zipped Zooid Altium files for Altium2KiCAD
2018-10-20 Zipped Altium Receiver files for Altium2KiCAD
2018-10-20 Add the 'price-calc' Numbers spreadsheet
2018-10-20 Updated Folder structure, deleted unnecessary gerber/PCB files
2018-10-21 File and BOM Updates
    Updated BOM to include printed parts, pcb etching, tools, projector(s), and touch sensor;
    Added KiCAD files for Touch Sensor
2018-10-21 Minor bom update
    Added playing surface notes
2018-10-21 Added Go programming resources/gits
    Text document with links
2018-10-21 Function/programming/theory doc updates
    Added resources and swarm function ideas
2018-10-21 Reformatted to rtf to make github friendly
2018-10-21 Seeing what can be viewable in github
2018-10-21 pain to read
2018-10-21 cant read in browser
2018-10-21 redundant
2018-10-21 Name change to doc
2018-10-21 Notes in BOM, removed doc that wasn't readable in brower on github
2018-10-21 Added vid to README showing functions
2018-10-21 Creating semi-separate workspace to make a BadukBot with smaller footprint and larger battery capacity
2018-10-21 Added prototype idea for smaller bot; Small run manufacturing resources
2018-10-21 Proto files added
2018-10-21 Added Reflow setup
2018-10-21 Link added for main log
2018-10-21 Working on making a smaller bot for better projection space management
2018-10-22 Converting Altium Schematic pdf to KiCAD Schematic
2018-10-22 Completed KiCAD Schematic
2018-10-23 BOM updates; Converted Altium Schematics pdf to KiCAD; New PCB design; First pass at routing with FreeRouting
2018-10-23 Changes to the Readme relevant to the BadukBot and GoSwarm project
2018-10-23 more of the same
2018-10-23 update to acknowledgements
2018-10-24 PCB adjustments
2018-10-24 readme updates
2018-10-24 renamed proto folder to BadukBot
2018-10-24 directory change/organization
2018-10-24 readme update
2018-10-24 revert directory change
2018-10-24 schematic/pcb changes
2018-10-25 More work on the PCB
2018-10-25 Original board layer images added; Experiments with trace routing using FreeRouting and component placement in KiCAD
2018-10-25 Added BadukBot sketch
2018-10-25 Updated sketch; added other images/video
2018-10-25 images added
2018-10-25 link updates
2018-10-26 Board adjustments for main board and topboard connectors
2018-10-26 Added graphics and logos for silk screen
2018-10-28 Images of original board's layers; images of current work setup; updated schematics and BOM to change connectors; major boards revisions
2018-10-30 Routed PCBs pending optimization
2018-10-31 Updates to the BOM; PCB changes
2018-11-02 Updated copper cores; changed schematic naming flags for 3rd party BOM generator; added renders of board; added some datasheets
2018-11-03 Added images of the board; minor changes to BOM; Attempts to use KiCost to automate component shopping; Minor changes to copper pours on board
    Working on getting KiCost to work with the xml generated by KiCAD to make shopping for parts easy at Octopart. Looks to be approx $20 per board
2018-11-03 Rearranging files
2018-11-04 Changed PCB for more compact component placement, shortened board 3, added images for the new layout
2018-11-04 Reduced board sizes, results in $6 saved per 3 boards at OSHPark
2018-11-04 Minor silk screen changes
2018-11-04 Added images of v3 of the board
2018-11-04 Added v3 images
2018-11-04 Changed folder naming
2018-11-06 board pics
2018-11-09 PCB revisions
2018-12-02 Changes to the PCBs for manufacturing
2018-12-02 Added pic of first batch of prototype boards

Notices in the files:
SKINNY_PROTOTYPE/BB_Hardware/PCB/BadukBot/BotSchematic/BotSchematicRouted_v02.kicad_pcb:
Licensed CC-BY-SA 4.0 By Caleb Cover
parts and their libraries:
Copyright 2016 Accelerated Designs. All rights reserved.
